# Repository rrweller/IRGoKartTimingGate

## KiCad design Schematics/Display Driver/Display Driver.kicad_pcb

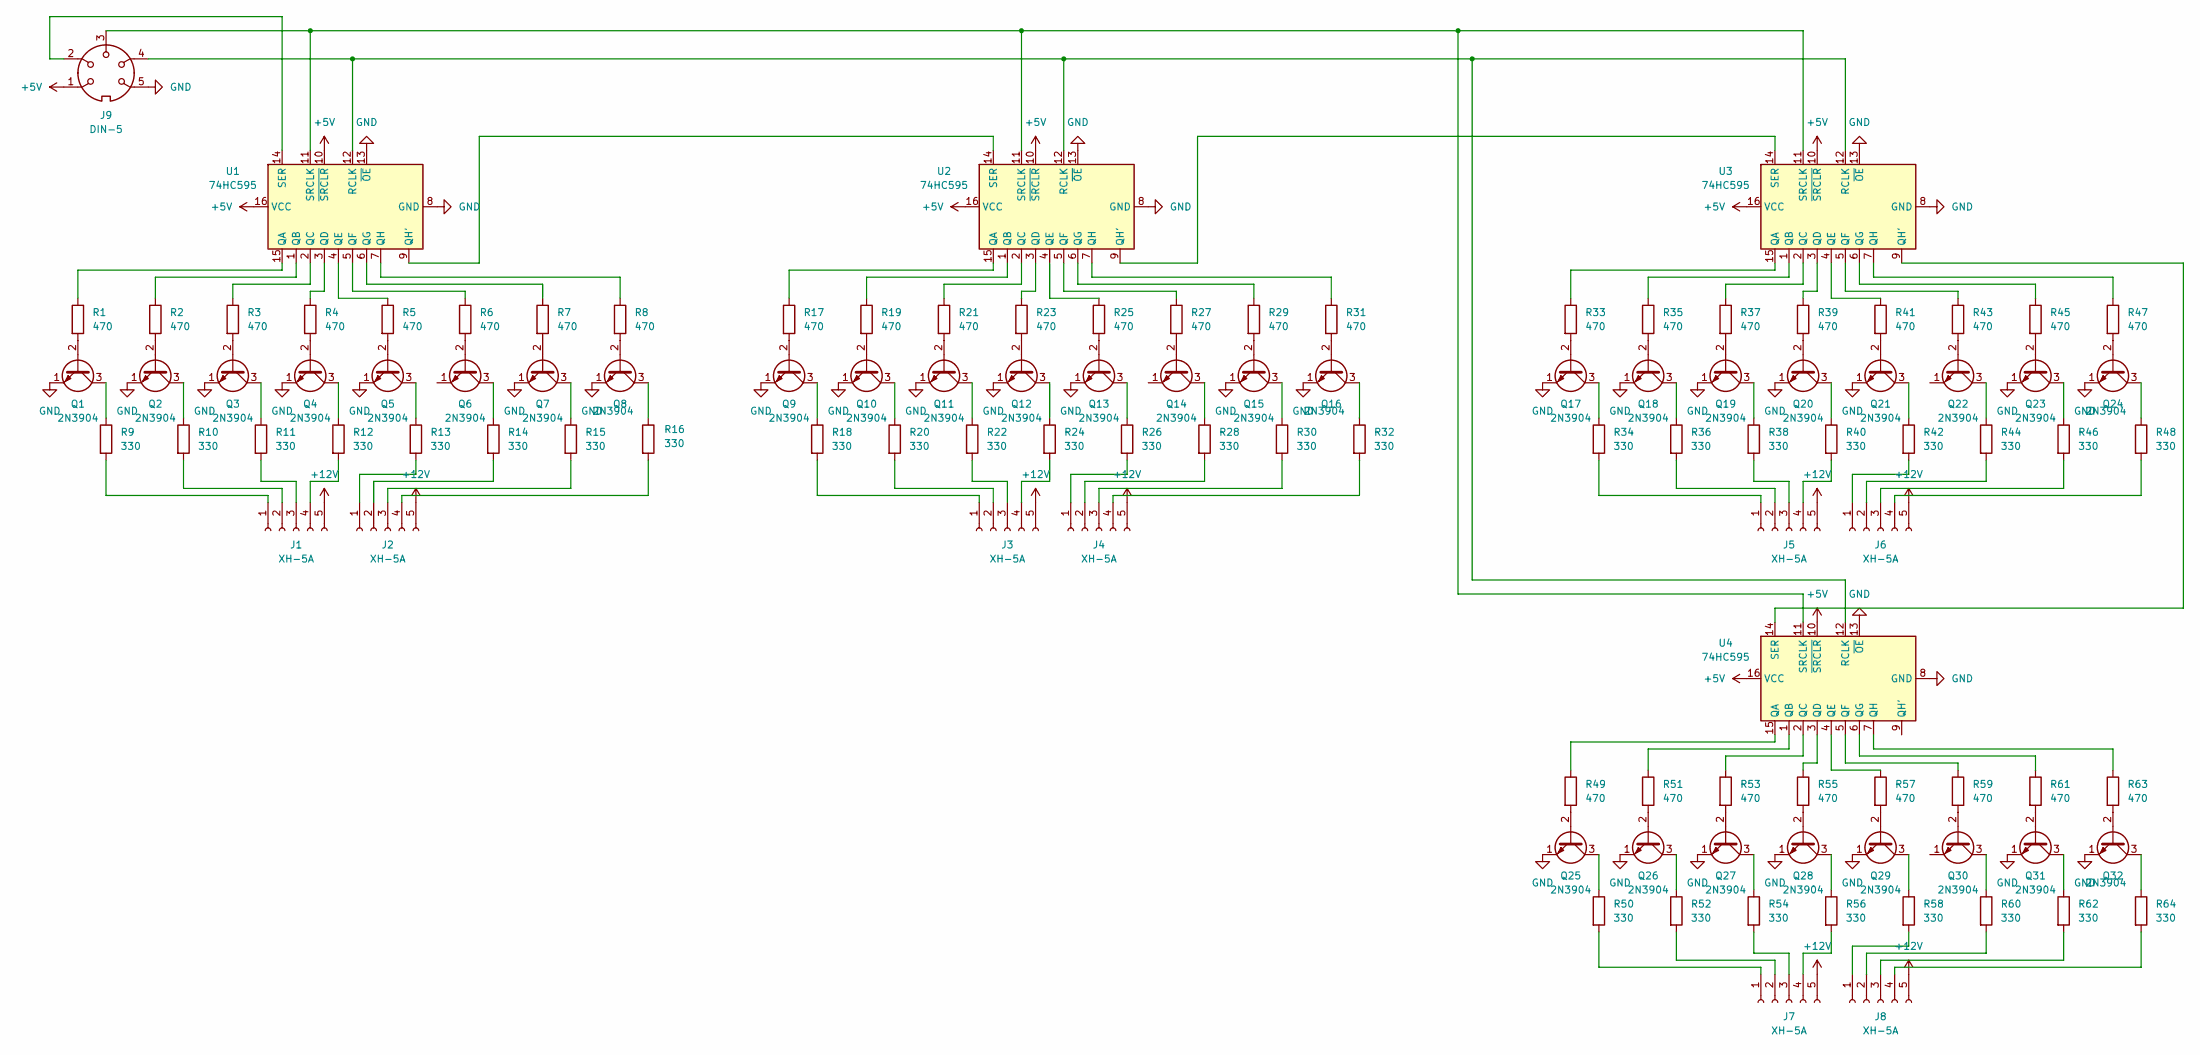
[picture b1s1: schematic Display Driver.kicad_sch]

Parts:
J1, J2, J3, J4, J5, J6, J7, J8: XH-5A; JST_XH_B5B-XH-A_1x05_P2.50mm_Vertical
J9: DIN-5; JST_XH_B5B-XH-A_1x05_P2.50mm_Vertical
Q1, Q2, Q3, Q4, Q5, Q6, Q7, Q8, Q9, Q10, Q11, Q12, Q13, Q14, Q15, Q16, Q17, Q18, Q19, Q20, Q21, Q22, Q23, Q24, Q25, Q26, Q27, Q28, Q29, Q30, Q31, Q32: 2N3904; TO-92_Inline
R1, R2, R3, R4, R5, R6, R7, R8, R17, R19, R21, R23, R25, R27, R29, R31, R33, R35, R37, R39, R41, R43, R45, R47, R49, R51, R53, R55, R57, R59, R61, R63: 470; R_Axial_DIN0207_L6.3mm_D2.5mm_P10.16mm_Horizontal
R9, R10, R11, R12, R13, R14, R15, R16, R18, R20, R22, R24, R26, R28, R30, R32, R34, R36, R38, R40, R42, R44, R46, R48, R50, R52, R54, R56, R58, R60, R62, R64: 330; R_Axial_DIN0207_L6.3mm_D2.5mm_P10.16mm_Horizontal
U1, U2, U3, U4: 74HC595; DIP-16_W7.62mm

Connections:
+5V: J9.1, U1.10 (~SRCLR), U1.16 (VCC), U2.10 (~SRCLR), U2.16 (VCC), U3.10 (~SRCLR), U3.16 (VCC), U4.10 (~SRCLR), U4.16 (VCC)
+12V: J1.5, J2.5, J3.5, J4.5, J5.5, J6.5, J7.5, J8.5
GND: J9.5, Q1.1 (E), Q2.1 (E), Q3.1 (E), Q4.1 (E), Q5.1 (E), Q7.1 (E), Q8.1 (E), Q9.1 (E), Q10.1 (E), Q11.1 (E), Q12.1 (E), Q13.1 (E), Q15.1 (E), Q16.1 (E), Q17.1 (E), Q18.1 (E), Q19.1 (E), Q20.1 (E), Q21.1 (E), Q23.1 (E), Q24.1 (E), Q25.1 (E), Q26.1 (E), Q27.1 (E), Q28.1 (E), Q29.1 (E), Q31.1 (E), Q32.1 (E), U1.8 (GND), U1.13 (~OE), U2.8 (GND), U2.13 (~OE), U3.8 (GND), U3.13 (~OE), U4.8 (GND), U4.13 (~OE)
unnamed: J1.1, R9.2
unnamed: J1.2, R10.2
unnamed: J1.3, R11.2
unnamed: J1.4, R12.2
unnamed: J2.1, R13.2
unnamed: J2.2, R14.2
unnamed: J2.3, R15.2
unnamed: J2.4, R16.2
unnamed: J3.1, R18.2
unnamed: J3.2, R20.2
unnamed: J3.3, R22.2
unnamed: J3.4, R24.2
unnamed: J4.1, R26.2
unnamed: J4.2, R28.2
unnamed: J4.3, R30.2
unnamed: J4.4, R32.2
unnamed: J5.1, R34.2
unnamed: J5.2, R36.2
unnamed: J5.3, R38.2
unnamed: J5.4, R40.2
unnamed: J6.1, R42.2
unnamed: J6.2, R44.2
unnamed: J6.3, R46.2
unnamed: J6.4, R48.2
unnamed: J7.1, R50.2
unnamed: J7.2, R52.2
unnamed: J7.3, R54.2
unnamed: J7.4, R56.2
unnamed: J8.1, R58.2
unnamed: J8.2, R60.2
unnamed: J8.3, R62.2
unnamed: J8.4, R64.2
unnamed: Q1.2 (B), R1.2
unnamed: Q1.3 (C), R9.1
unnamed: Q2.2 (B), R2.2
unnamed: Q2.3 (C), R10.1
unnamed: Q3.2 (B), R3.2
unnamed: Q3.3 (C), R11.1
unnamed: Q4.2 (B), R4.2
unnamed: Q4.3 (C), R12.1
unnamed: Q5.2 (B), R5.2
unnamed: Q5.3 (C), R13.1
unnamed: Q6.2 (B), R6.2
unnamed: Q6.3 (C), R14.1
unnamed: Q7.2 (B), R7.2
unnamed: Q7.3 (C), R15.1
unnamed: Q8.2 (B), R8.2
unnamed: Q8.3 (C), R16.1
unnamed: Q9.2 (B), R17.2
unnamed: Q9.3 (C), R18.1
unnamed: Q10.2 (B), R19.2
unnamed: Q10.3 (C), R20.1
unnamed: Q11.2 (B), R21.2
unnamed: Q11.3 (C), R22.1
unnamed: Q12.2 (B), R23.2
unnamed: Q12.3 (C), R24.1
unnamed: Q13.2 (B), R25.2
unnamed: Q13.3 (C), R26.1
unnamed: Q14.2 (B), R27.2
unnamed: Q14.3 (C), R28.1
unnamed: Q15.2 (B), R29.2
unnamed: Q15.3 (C), R30.1
unnamed: Q16.2 (B), R31.2
unnamed: Q16.3 (C), R32.1
unnamed: Q17.2 (B), R33.2
unnamed: Q17.3 (C), R34.1
unnamed: Q18.2 (B), R35.2
unnamed: Q18.3 (C), R36.1
unnamed: Q19.2 (B), R37.2
unnamed: Q19.3 (C), R38.1
unnamed: Q20.2 (B), R39.2
unnamed: Q20.3 (C), R40.1
unnamed: Q21.2 (B), R41.2
unnamed: Q21.3 (C), R42.1
unnamed: Q22.2 (B), R43.2
unnamed: Q22.3 (C), R44.1
unnamed: Q23.2 (B), R45.2
unnamed: Q23.3 (C), R46.1
unnamed: Q24.2 (B), R47.2
unnamed: Q24.3 (C), R48.1
unnamed: Q25.2 (B), R49.2
unnamed: Q25.3 (C), R50.1
unnamed: Q26.2 (B), R51.2
unnamed: Q26.3 (C), R52.1
unnamed: Q27.2 (B), R53.2
unnamed: Q27.3 (C), R54.1
unnamed: Q28.2 (B), R55.2
unnamed: Q28.3 (C), R56.1
unnamed: Q29.2 (B), R57.2
unnamed: Q29.3 (C), R58.1
unnamed: Q30.2 (B), R59.2
unnamed: Q30.3 (C), R60.1
unnamed: Q31.2 (B), R61.2
unnamed: Q31.3 (C), R62.1
unnamed: Q32.2 (B), R63.2
unnamed: Q32.3 (C), R64.1
unnamed: R1.1, U1.15 (QA)
unnamed: R2.1, U1.1 (QB)
unnamed: R3.1, U1.2 (QC)
unnamed: R4.1, U1.3 (QD)
unnamed: R5.1, U1.4 (QE)
unnamed: R6.1, U1.5 (QF)
unnamed: R7.1, U1.6 (QG)
unnamed: U1.9 (QH'), U2.14 (SER)
unnamed: R8.1, U1.7 (QH)
unnamed: J9.4, U1.12 (RCLK), U2.12 (RCLK), U3.12 (RCLK), U4.12 (RCLK)
unnamed: J9.2, U1.14 (SER)
unnamed: J9.3, U1.11 (SRCLK), U2.11 (SRCLK), U3.11 (SRCLK), U4.11 (SRCLK)
unnamed: R17.1, U2.15 (QA)
unnamed: R19.1, U2.1 (QB)
unnamed: R21.1, U2.2 (QC)
unnamed: R23.1, U2.3 (QD)
unnamed: R25.1, U2.4 (QE)
unnamed: R27.1, U2.5 (QF)
unnamed: R29.1, U2.6 (QG)
unnamed: U2.9 (QH'), U3.14 (SER)
unnamed: R31.1, U2.7 (QH)
unnamed: R33.1, U3.15 (QA)
unnamed: R35.1, U3.1 (QB)
unnamed: R37.1, U3.2 (QC)
unnamed: R39.1, U3.3 (QD)
unnamed: R41.1, U3.4 (QE)
unnamed: R43.1, U3.5 (QF)
unnamed: R45.1, U3.6 (QG)
unnamed: U3.9 (QH'), U4.14 (SER)
unnamed: R47.1, U3.7 (QH)
unnamed: R49.1, U4.15 (QA)
unnamed: R51.1, U4.1 (QB)
unnamed: R53.1, U4.2 (QC)
unnamed: R55.1, U4.3 (QD)
unnamed: R57.1, U4.4 (QE)
unnamed: R59.1, U4.5 (QF)
unnamed: R61.1, U4.6 (QG)
unnamed: R63.1, U4.7 (QH)

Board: 2 copper layers, 109 parts (0 on the bottom side), 137 nets, no tracks yet.

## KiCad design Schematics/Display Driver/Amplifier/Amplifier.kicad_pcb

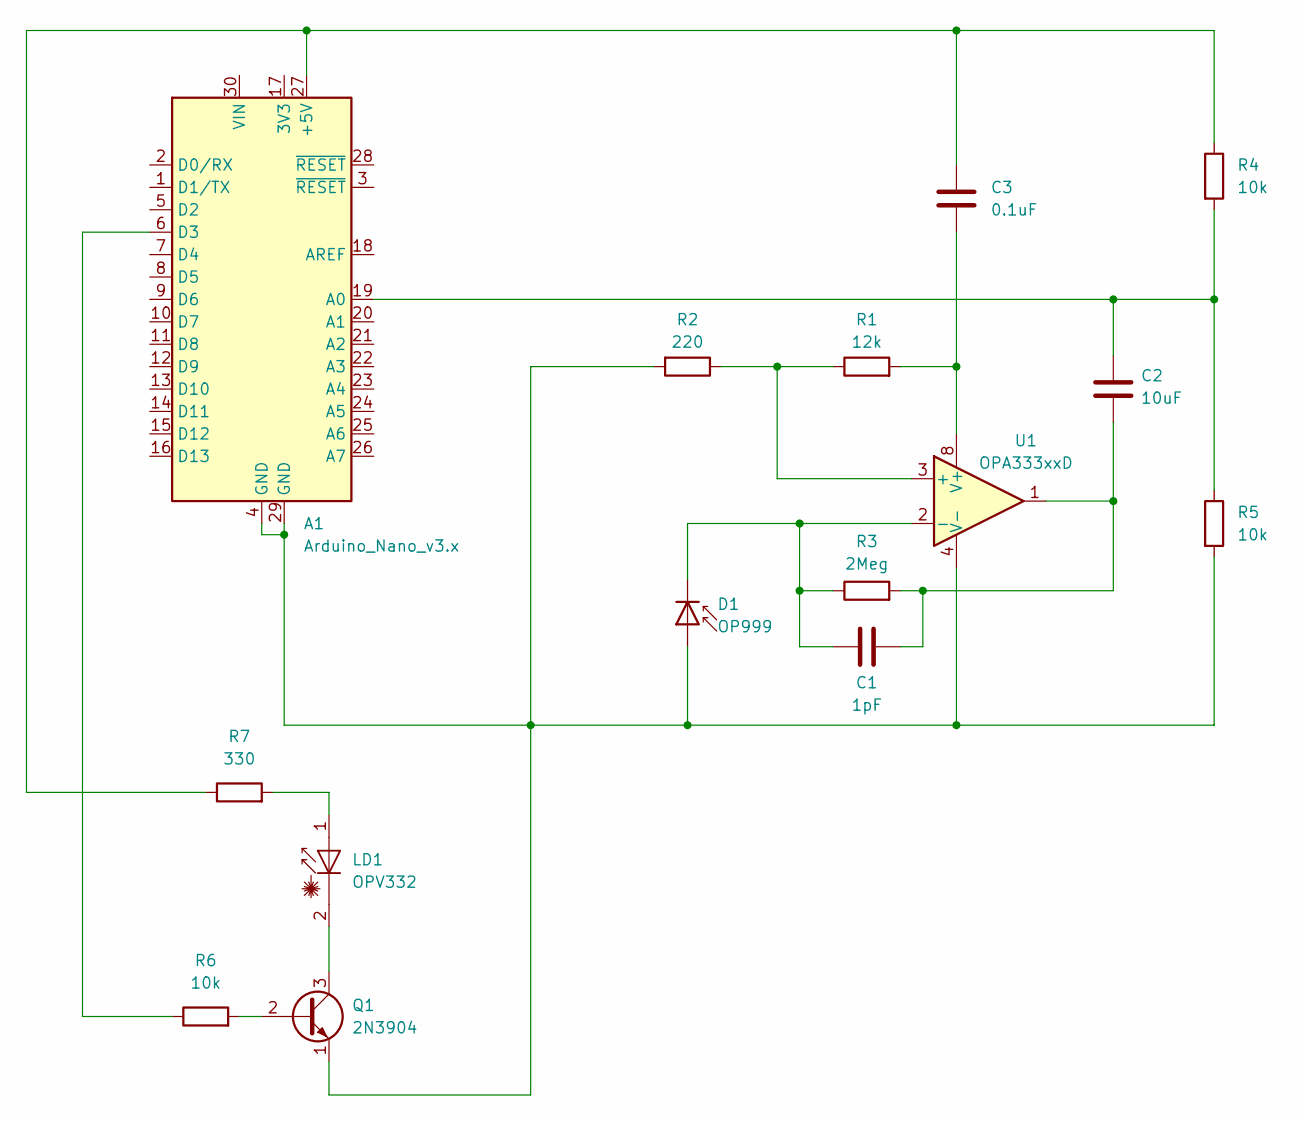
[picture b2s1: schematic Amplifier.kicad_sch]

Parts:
A1: Arduino_Nano_v3.x; Arduino_Nano
C1: 1pF; C_Disc_D5.0mm_W2.5mm_P5.00mm
C2: 10uF; C_Disc_D5.0mm_W2.5mm_P5.00mm
C3: 0.1uF; C_Disc_D5.0mm_W2.5mm_P5.00mm
D1: OP999; LED_D5.0mm_Horizontal_O3.81mm_Z3.0mm
LD1: OPV332; LED_D3.0mm_Horizontal_O3.81mm_Z2.0mm
Q1: 2N3904; TO-92_Inline
R1: 12k; R_Axial_DIN0207_L6.3mm_D2.5mm_P10.16mm_Horizontal
R2: 220; R_Axial_DIN0207_L6.3mm_D2.5mm_P10.16mm_Horizontal
R3: 2Meg; R_Axial_DIN0207_L6.3mm_D2.5mm_P10.16mm_Horizontal
R4, R5, R6: 10k; R_Axial_DIN0207_L6.3mm_D2.5mm_P10.16mm_Horizontal
R7: 330; R_Axial_DIN0207_L6.3mm_D2.5mm_P10.16mm_Horizontal
U1: OPA333xxD; SOIC-8_3.9x4.9mm_P1.27mm

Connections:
unnamed: A1.27 (+5V), C3.1, R4.1, R7.1
unnamed: A1.19 (A0), C2.1, R4.2, R5.1
unnamed: A1.6 (D3), R6.1
unnamed: C1.1, C2.2, R3.2, U1.1 (NC)
unnamed: A1.4 (GND), A1.29 (GND), D1.2 (A), Q1.1 (E), R2.2, R5.2, U1.4 (V-)
unnamed: C1.2, D1.1 (K), R3.1, U1.2 (-)
unnamed: LD1.1 (A), R7.2
unnamed: LD1.2 (K), Q1.3 (C)
unnamed: Q1.2 (B), R6.2
unnamed: R1.1, R2.1, U1.3 (+)
unnamed: C3.2, R1.2, U1.8 (V+)

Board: 2 copper layers, 15 parts (0 on the bottom side), 11 nets, no tracks yet.

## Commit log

2025-02-22 spice
2025-02-22 start of circuit
2025-02-26 PWM signal
2025-03-03 init schematics
2025-03-09 starting on pcbs
2025-05-20 pre-code committ
2025-05-20 init of real code
2025-05-20 logging output
2025-05-20 working red digits
2025-05-20 everything working
2025-05-20 ready state
    doesnt work yet but need to figure out detection logic first
2025-05-22 debug print lines
    detecting things and printing strength and Vpp
2025-05-22 working detection and lap timing
    it works!
2025-05-22 good version
    no apparent bugs, everything is working as it should
2025-05-22 added error state and state text display
2025-05-22 tweaks and comment cleanup
2025-05-24 implemented raw ADC value to test saturation
2025-05-24 revert code, update CAD with filter hole. still uses shroud though
2025-05-24 signal improvements test
2025-05-24 Revert "signal improvements test"
    This reverts commit 7c50058911214bd4ec637a36dd634ae96a98c77d.
2025-05-24 signal improvements try 2
2025-05-24 attempt again at signal detection improvements
2025-05-24 attempt at faster sample rate
2025-05-24 fixed lv and %
    test this codes timing
2025-05-31 inplace changes
2025-05-31 Revert "inplace changes"
    This reverts commit 159bbc458993052cacbf1772d8e8c399ba6646a3.
2025-05-31 CAD changes
